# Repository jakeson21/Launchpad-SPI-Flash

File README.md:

# Launchpad-SPI-Flash
SOIC-8 SPI Flash Memory Launchpad Carrier

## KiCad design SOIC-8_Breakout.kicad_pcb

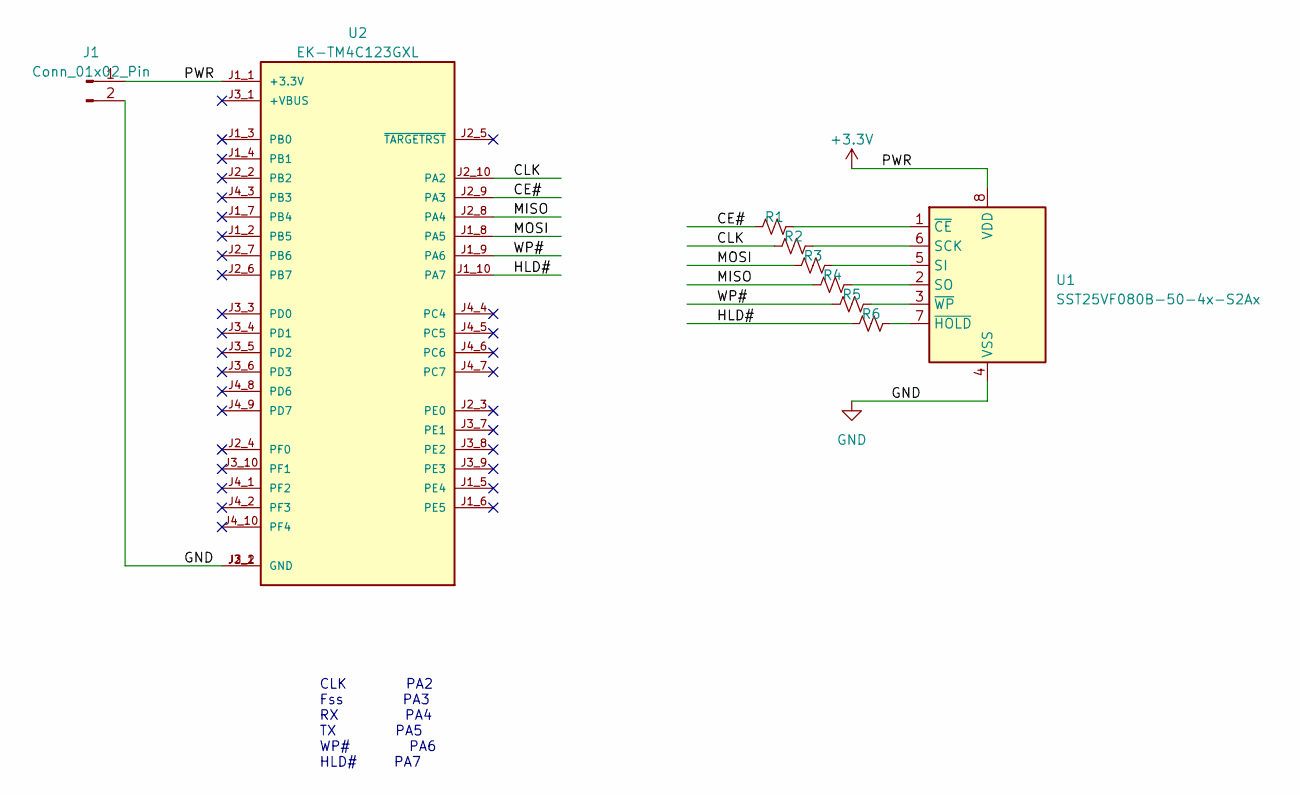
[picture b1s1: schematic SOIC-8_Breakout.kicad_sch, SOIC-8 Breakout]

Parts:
J1: Conn_01x02_Pin; PinHeader_1x02_P2.54mm_Vertical
R1, R2, R3, R4, R5, R6: R_Small_US; R_0805_2012Metric_Pad1.20x1.40mm_HandSolder
U1: SST25VF080B-50-4x-S2Ax; SOIC-8_5.275x5.275mm_P1.27mm
U2: EK-TM4C123GXL; MODULE_EK-TM4C123GXL; PARTREV April 2013

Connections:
+3.3V: J1.1, U1.8 (VDD), U2.J1_1 (+3.3V)
/CE#: R1.1, U2.J2_9 (PA3)
/CLK: R2.2, U2.J2_10 (PA2)
/HLD#: R6.2, U2.J1_10 (PA7)
/MISO: R4.2, U2.J2_8 (PA4)
/MOSI: R3.2, U2.J1_8 (PA5)
/WP#: R5.2, U2.J1_9 (PA6)
GND: J1.2, U1.4 (VSS), U2.J2_1 (GND), U2.J3_2 (GND)
unnamed: R2.1, U1.6 (SCK)
unnamed: R3.1, U1.5 (SI)
unnamed: R4.1, U1.2 (SO)
unnamed: R1.2, U1.1 (~CE)
unnamed: R6.1, U1.7 (~HOLD)
unnamed: R5.1, U1.3 (~WP)

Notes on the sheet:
CLK PA2 Fss PA3 RX PA4 TX PA5 WP# PA6 HLD# PA7

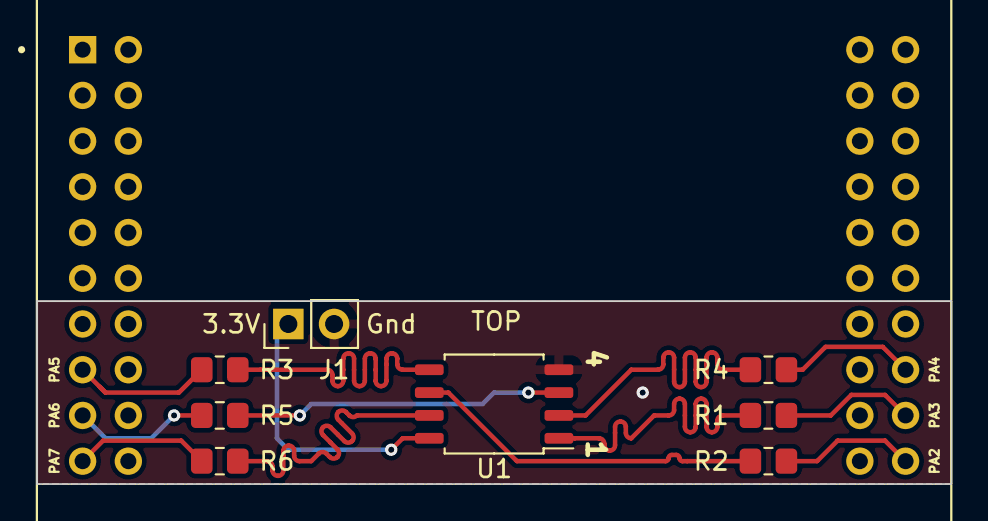
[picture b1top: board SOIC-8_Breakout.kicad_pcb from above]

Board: 2 copper layers, 50.8 x 10.2 mm, 9 parts (0 on the bottom side), 14 nets.
